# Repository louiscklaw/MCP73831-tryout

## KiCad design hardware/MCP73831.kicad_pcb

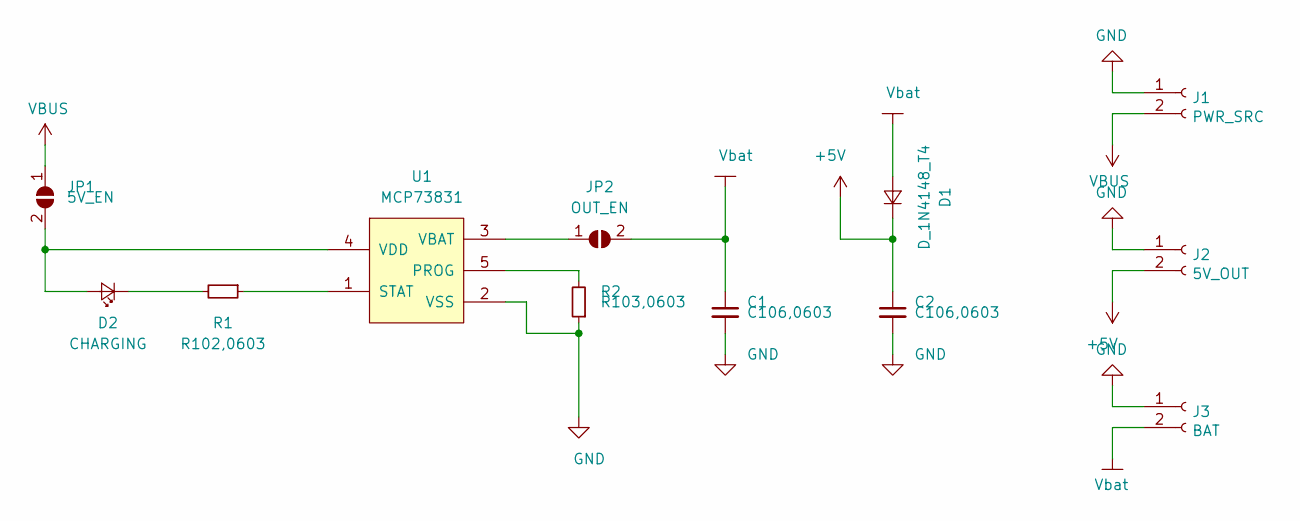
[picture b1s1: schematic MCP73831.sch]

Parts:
C1, C2: C106,0603; C_0603_1608Metric_Pad1.05x0.95mm_HandSolder
D1: D_1N4148_T4; D_SOD-123
D2: CHARGING; LED_0603_1608Metric
J1: PWR_SRC; PinHeader_1x02_P2.54mm_Vertical
J2: 5V_OUT; PinHeader_1x02_P2.54mm_Vertical
J3: BAT; PinHeader_1x02_P2.54mm_Vertical
JP1: 5V_EN; SolderJumper-2_P1.3mm_Open_RoundedPad1.0x1.5mm
JP2: OUT_EN; SolderJumper-2_P1.3mm_Open_RoundedPad1.0x1.5mm
R1: R102,0603; R_0603_1608Metric_Pad1.05x0.95mm_HandSolder
R2: R103,0603; R_0603_1608Metric_Pad1.05x0.95mm_HandSolder
U1: MCP73831; MCP73831_SOT23_5

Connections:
+5V: C2.1, D1.1 (K), J2.2
GND: C1.2, C2.2, J1.1, J2.1, J3.1, R2.1, U1.2 (VSS)
unnamed: D2.1 (K), R1.2
unnamed: D2.2 (A), JP1.2 (B), U1.4 (VDD)
unnamed: JP2.1 (A), U1.3 (VBAT)
unnamed: R1.1, U1.1 (STAT)
unnamed: R2.2, U1.5 (PROG)
VBUS: J1.2, JP1.1 (A)
Vbat: C1.1, D1.2 (A), J3.2, JP2.2 (B)

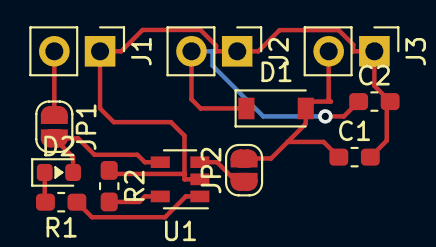
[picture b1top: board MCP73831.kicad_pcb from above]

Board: 2 copper layers, 12 parts (0 on the bottom side), 9 nets.

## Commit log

2019-06-11 repair MCP73831,
2019-06-11 update to repair MCP73831,
2019-06-16 update,
2020-05-06 ci: init travis build config,
2020-05-06 ci: init travis token,
